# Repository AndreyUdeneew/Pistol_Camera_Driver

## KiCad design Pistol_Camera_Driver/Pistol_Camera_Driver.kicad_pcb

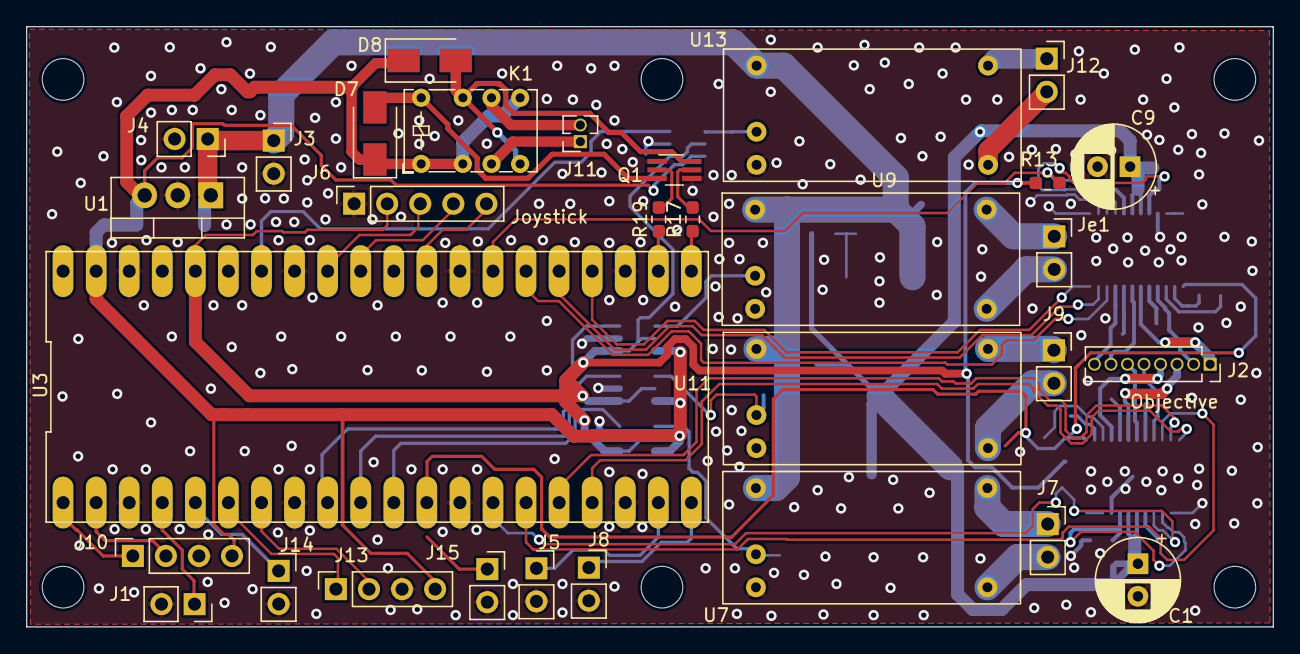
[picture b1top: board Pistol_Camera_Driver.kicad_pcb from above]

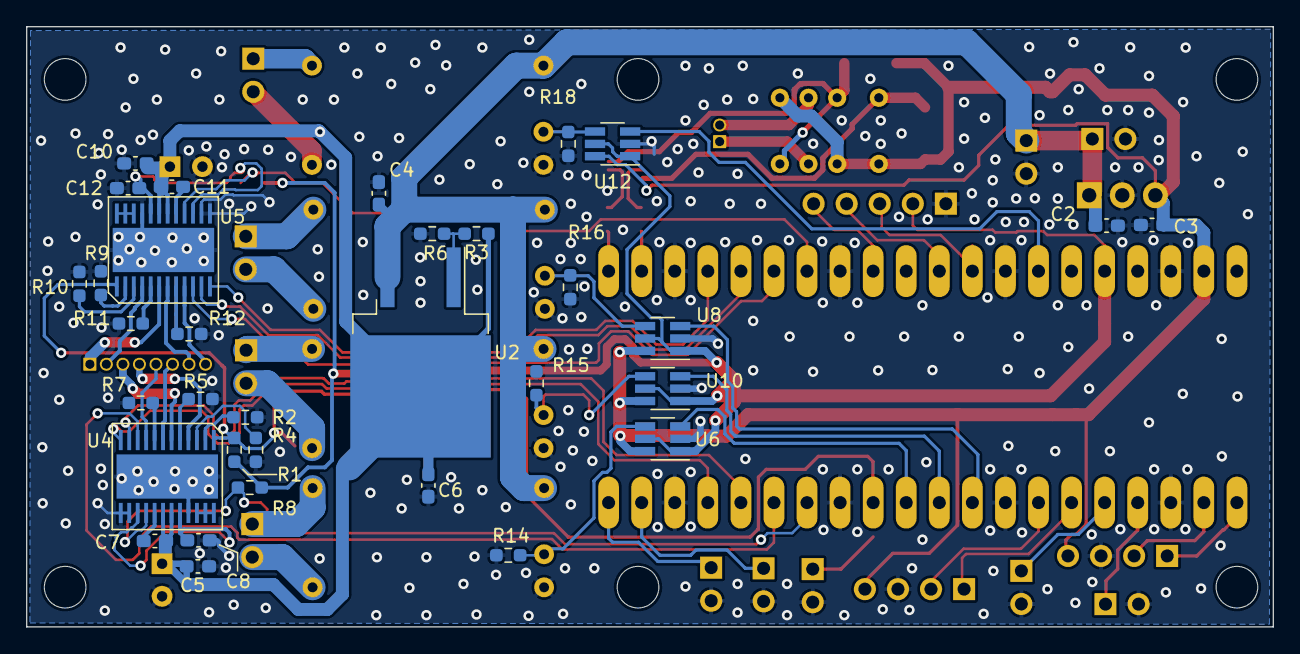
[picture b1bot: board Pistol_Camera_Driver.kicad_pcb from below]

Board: 2 copper layers, 95.8 x 46.1 mm, 64 parts (33 on the bottom side), 72 nets.

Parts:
C1, C9: 10uF; CP_Radial_D6.3mm_P2.50mm
C2: 0.33; C_0603_1608Metric_Pad1.08x0.95mm_HandSolder
C3, C5, C10: 0.1; C_0603_1608Metric_Pad1.08x0.95mm_HandSolder
C4, C6: 1; C_0603_1608Metric_Pad1.08x0.95mm_HandSolder
C7, C11: 0.01; C_0603_1608Metric_Pad1.08x0.95mm_HandSolder
C8, C12: 2.2; C_0603_1608Metric_Pad1.08x0.95mm_HandSolder
D7, D8: CDBA3100-HF; D_SMA
J1, J3, J4, J5, J7, J8, J9, J12, J14, J15: Screw_Terminal_01x02; PinSocket_1x02_P2.54mm_Vertical
J2: Objective; PinSocket_1x08_P1.27mm_Vertical
J6: Joystick; PinSocket_1x05_P2.54mm_Vertical
J10: Bluetooth; PinSocket_1x04_P2.54mm_Vertical
J11: Screw_Terminal_01x02; PinSocket_1x02_P1.27mm_Vertical
J13: I2C; PinSocket_1x04_P2.54mm_Vertical
Je1: Screw_Terminal_01x02; PinSocket_1x02_P2.54mm_Vertical
K1: IM03; Relay_DPDT_AXICOM_IMSeries_Pitch5.08mm
Q1: locked; SOT-363_SC-70-6_Handsoldering
R1: 47k; R_0603_1608Metric_Pad0.98x0.95mm_HandSolder
R2, R4, R9, R10: 470; R_0603_1608Metric_Pad0.98x0.95mm_HandSolder
R3: 240; R_0603_1608Metric_Pad0.98x0.95mm_HandSolder
R5, R7, R11, R12: 3.9; R_0603_1608Metric_Pad0.98x0.95mm_HandSolder
R6: 390; R_0603_1608Metric_Pad0.98x0.95mm_HandSolder
R8, R14, R15, R18: 10k; R_0603_1608Metric_Pad0.98x0.95mm_HandSolder
R13, R16: 10 k; R_0603_1608Metric_Pad0.98x0.95mm_HandSolder
R17, R19: 1k; R_0603_1608Metric_Pad0.98x0.95mm_HandSolder
U1: LM7805_TO220; TO-220-3_Vertical
U2: LM317_TO-263; TO-263-2
U3: Raspberri_Pi_Pico; Raspberry Pi Pico
U4, U5: DRV8834PWP
U6, U8, U10, U12: RS0101YH6; SOT-23-6_Handsoldering
U7, U9, U11, U13: LDD-700L

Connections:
+3.3VP: C1.1, C5.2, C6.1, C7.2, C9.1, C10.1, C11.2, R3.1, U2.2 (VO), U4.18 (VM), U4.19 (VM), U5.18 (VM), U5.19 (VM)
+3V3: J6.2, R1.1, R8.1, R13.1, U3.36 (3V3_OUT), U6.1 (VCCA), U6.5 (OE), U8.1 (VCCA), U8.5 (OE), U10.1 (VCCA), U10.5 (OE), U12.1 (VCCA), U12.5 (OE)
+5V: C3.1, D7.1 (K), D8.1 (K), J10.4, J13.4, K1.1, K1.2, K1.5, U1.3 (VO), U3.39 (VSYS), U6.6 (VCCB), U8.6 (VCCB), U10.6 (VCCB), U12.6 (VCCB)
+12V: C2.1, C4.1, J3.1, J4.1, U1.1 (VI), U2.3 (VI), U7.1 (Vin+), U9.1 (Vin+), U11.1 (Vin+), U13.1 (Vin+)
AOUT1_1: J2.4, U4.4 (AOUT1)
AOUT1_2: J2.2, U5.4 (AOUT1)
AOUT2_1: J2.3, U4.6 (AOUT2)
AOUT2_2: J2.1, U5.6 (AOUT2)
BOUT1_1: J2.5, U4.9 (BOUT1)
BOUT1_2: J2.8, U5.9 (BOUT1)
BOUT2_1: J2.6, U4.7 (BOUT2)
BOUT2_2: J2.7, U5.7 (BOUT2)
DIR1: U3.17 (GP13), U4.12 (DIR)
DIR2: U3.24 (GP18/SCK), U5.12 (DIR)
GND: C1.2, C2.2, C3.2, C4.2, C5.1, C6.2, C8.2, C9.2, C10.2, C12.2, J1.2, J3.2, J4.2, J5.2, J6.1, J8.2, J10.3, J13.3, J14.2, J15.2, Q1.1 (E1), Q1.4 (E2), R2.1, R4.1, R5.1, R6.2, R7.1, R9.1, R10.1, R11.1, R12.1, R14.2, R15.2, R16.2, R18.2, U1.2 (GND), U3.3 (GND), U3.8 (GND), U3.13 (GND), U3.18 (GND), U3.23 (GND), U3.28 (GND), U3.33 (AGND), U3.38 (GND), U4.13 (M0), U4.14 (M1), U4.21 (GND), U4.25 (GND), U5.13 (M0), U5.14 (M1), U5.21 (GND), U5.25 (GND), U6.2 (GND), U7.3 (Vin-), U8.2 (GND), U9.3 (Vin-), U10.2 (GND), U11.3 (Vin-), U12.2 (GND), U13.3 (Vin-)
K1: J5.1, U3.19 (GP14)
K2: J8.1, U3.20 (GP15)
K3: J14.1, U3.5 (GP3)
MOTORS_nSLEEP: R1.2, U3.12 (GP9), U4.1 (nSLEEP), U5.1 (nSLEEP)
unnamed: C7.1, U4.17 (VCP)
unnamed: C8.1, U4.15 (CONFIG), U4.20 (VINT)
unnamed: C11.1, U5.17 (VCP)
unnamed: C12.1, U5.15 (CONFIG), U5.20 (VINT)
unnamed: J7.1, U7.5 (Vout+)
unnamed: J7.2, U7.4 (Vout-)
unnamed: Je1.1, U9.5 (Vout+)
unnamed: Je1.2, U9.4 (Vout-)
unnamed: J9.1, U11.5 (Vout+)
unnamed: J9.2, U11.4 (Vout-)
unnamed: D7.2 (A), K1.8, Q1.3 (C2)
unnamed: D8.2 (A), K1.4, K1.7, Q1.6 (C1)
unnamed: J12.1, U13.5 (Vout+)
unnamed: J12.2, U13.4 (Vout-)
unnamed: J11.1, K1.3
unnamed: J11.2, K1.6
unnamed: Q1.2 (B1), R19.2
unnamed: Q1.5 (B2), R17.2
unnamed: R2.2, U4.2 (BDECAY)
unnamed: R3.2, R6.1, U2.1 (ADJ)
unnamed: R4.2, U4.3 (ADECAY)
unnamed: R5.2, U4.5 (AISEN)
unnamed: R7.2, U4.8 (BISEN)
unnamed: R9.2, U5.2 (BDECAY)
unnamed: R10.2, U5.3 (ADECAY)
unnamed: R11.2, U5.5 (AISEN)
unnamed: R12.2, U5.8 (BISEN)
unnamed: R14.1, U6.4 (GPIOB), U7.2 (PWM)
unnamed: R15.1, U10.4 (GPIOB), U11.2 (PWM)
unnamed: R16.1, U8.4 (GPIOB), U9.2 (PWM)
unnamed: R18.1, U12.4 (GPIOB), U13.2 (PWM)
unnamed: U4.22 (AVREF), U4.23 (BVREF), U4.24 (VREFO)
unnamed: U5.22 (AVREF), U5.23 (BVREF), U5.24 (VREFO)
PWM_IR: U3.34 (GP28/ADC2), U12.3 (GPIOA)
PWM_RED: U3.10 (GP7), U10.3 (GPIOA)
PWM_UV: U3.11 (GP8), U6.3 (GPIOA)
PWM_WHITE: U3.9 (GP6), U8.3 (GPIOA)
RX: J10.1, U3.1 (GP0/TX)
SCL: J13.2, U3.7 (GP5/SCL)
SDA: J13.1, U3.6 (GP4/SDA)
STEP1: U3.16 (GP12), U4.11 (STEP)
STEP2: U3.25 (GP19/MOSI), U5.11 (STEP)
SW: J6.5, U3.29 (GP22)
Solenoid_DIR: R17.1, U3.21 (GP16/MISO)
Solenoid_ON: R19.1, U3.22 (GP17/CS)
Strobe Input: J1.1, U3.4 (GP2)
TX: J10.2, U3.2 (GP1/RX)
VarX: J6.4, U3.31 (GP26/ADC0)
VarY: J6.3, U3.32 (GP27/ADC1)
nEN1: U3.15 (GP11), U4.10 (nENBL)
nEN2: U3.26 (GP20), U5.10 (nENBL)
nFLT1: R8.2, U3.14 (GP10), U4.16 (nFAULT)
nFLT2: R13.2, U3.27 (GP21), U5.16 (nFAULT)

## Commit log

2022-12-16 v0.1 Initial circuit has been added
2022-12-16 v0.2 Circuit has been complemented
2022-12-17 v0.3 Circuit except the joystick has been completed
2022-12-17 v0.4 Footprints of DRV & RPI have been added
2022-12-17 v0.5 Joystick has been added
2022-12-19 v0.6 All the elements have been created
2022-12-19 v0.7 vircuit has been corrected
2022-12-19 v0.71 actual state
2023-01-17 v0.72 level translaors have been added
2023-01-28 v0.8 first decomposition is completed
2023-01-30 v0.9 PCB size has been decreased
2023-02-01 v1.0 decomposition has been completed. Partial routing
2023-02-01 v1.1 The first iteration of routing
2023-02-02 v1.2 The second routing iteration
2023-02-03 v1.3 seems 2B ready
2023-02-06 v1.4 Bluetooth was added, mounting holes were corrected. Seems 2B ready!
2023-02-09 v1.5 2 reserve connectors were added, cosmetical changes
2023-02-09 v1.6 cosmetic changes
2023-02-11 v1.7 ready 2 send
2023-02-11 v1.8 this variant is sent (with a civiloan name))
2023-02-18 v1.9 some nominals were added
2023-02-19 Auto stash before merge of "main" and "origin/main"
2023-02-19 Revert "v1.6 cosmetic changes"
    This reverts commit 11c83a201ecd707cf3e43ae6fa817195c0111334.
2023-02-19 v2.0 Circuit, PCB were corrected
2023-03-16 v2.1 pins were changed (I2C & PWM)
2023-03-18 v2.2 i2C ToА proto
2023-08-16 v2.3 Circuit was changed. (4 LEDs, Solenoid driver)
2023-08-18 v2.4 some nets were routed
2023-08-20 v2.5 ready without end stoppers
2023-08-21 v2.6 3 end stoppers were added into the circuit
2023-08-21 v2.7 stoppers were added into the scch and pcb
2023-08-22 v2.8 silk was corrected
2023-08-26 v2.8 Full featured, DRC, ordered
2023-10-11 v2.9 relay to 5 V, nMotorsSleep to RPI Pico
